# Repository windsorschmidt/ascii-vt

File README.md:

# About

Clone of Geoff Graham's ASCII video terminal. KiCad 5.2.

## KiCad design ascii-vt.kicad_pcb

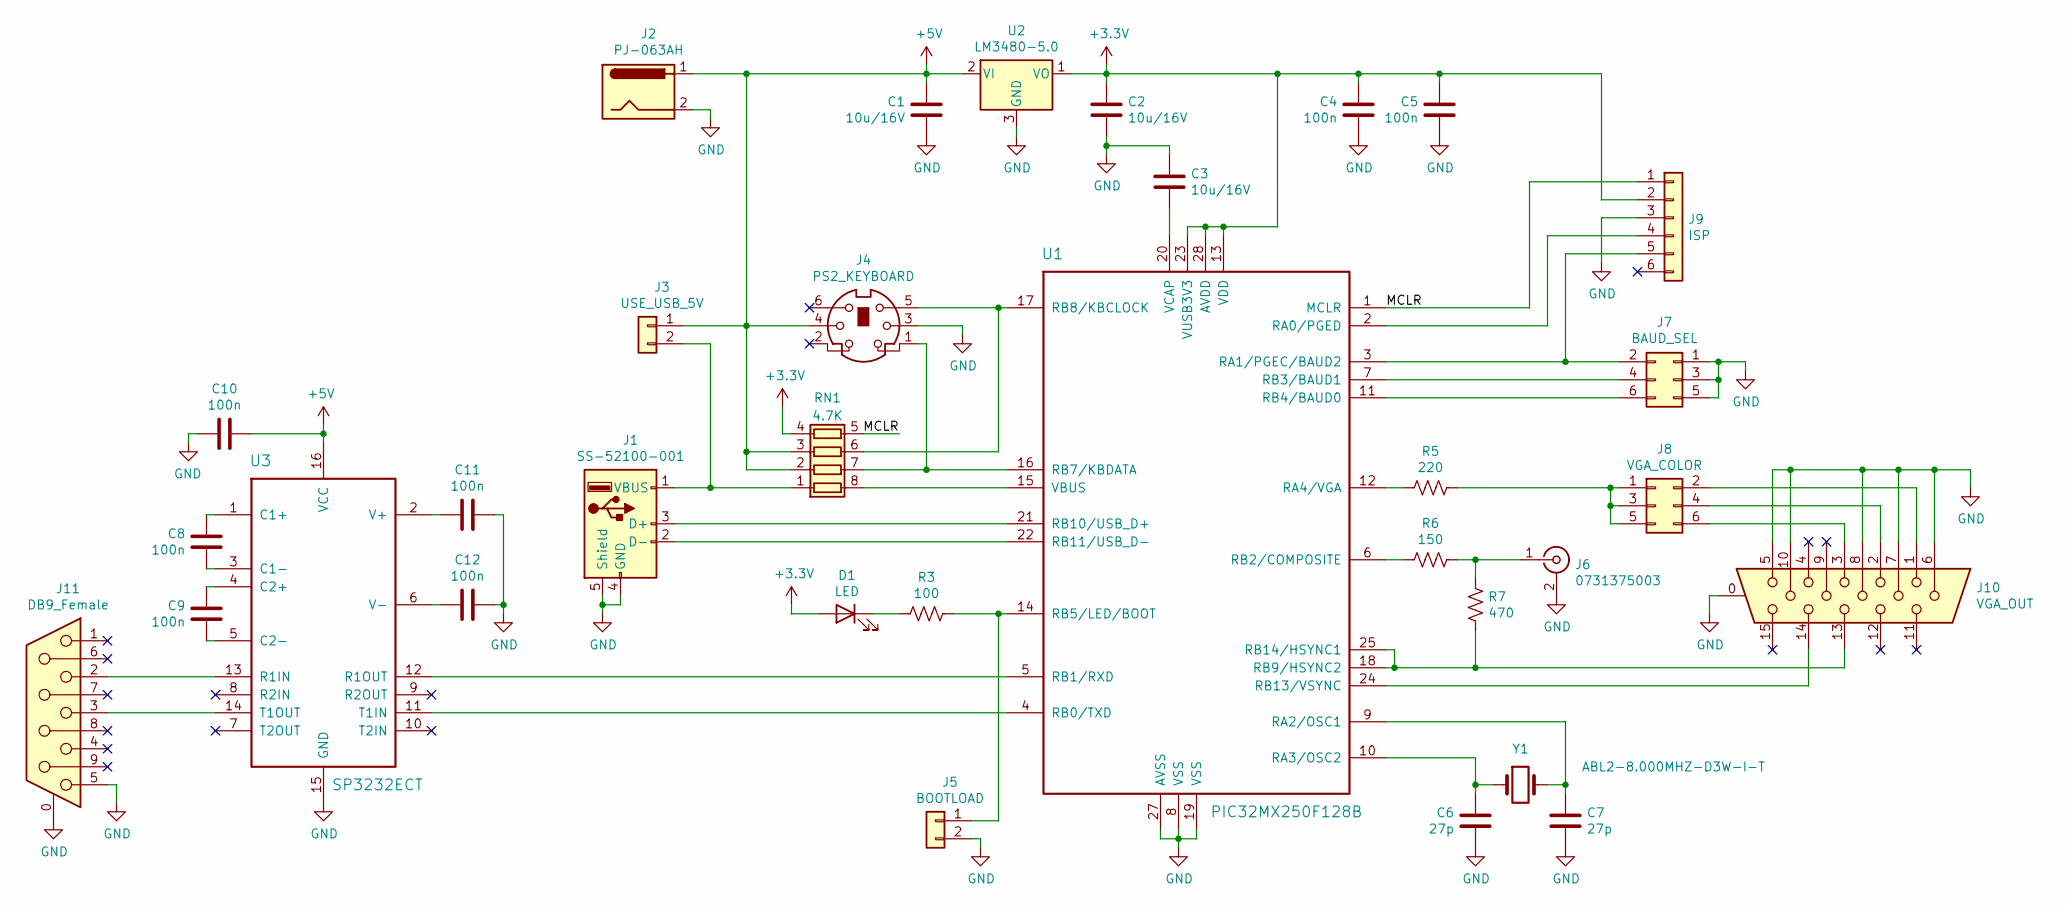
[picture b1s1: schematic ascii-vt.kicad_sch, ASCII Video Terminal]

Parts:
C1, C2, C3: 10u/16V; C_0805_2012Metric
C4, C5, C8, C9, C10, C11, C12: 100n; C_0805_2012Metric
C6, C7: 27p; C_0805_2012Metric
D1: LED; LED_0805_2012Metric
J1: SS-52100-001; USB_A_Stewart_SS-52100-001_Horizontal
J2: PJ-063AH; BarrelJack_CUI_PJ-063AH_Horizontal
J3: USE_USB_5V; PinHeader_1x02_P2.54mm_Vertical
J4: PS2_KEYBOARD; Connector_Mini-DIN_Female_6Pin_2rows
J5: BOOTLOAD; PinHeader_1x02_P2.54mm_Vertical
J6: 0731375003; BNC_Amphenol_B6252HB-NPP3G-50_Horizontal
J7: BAUD_SEL; PinHeader_2x03_P2.54mm_Vertical
J8: VGA_COLOR; PinHeader_2x03_P2.54mm_Vertical
J9: ISP; PinHeader_1x06_P2.54mm_Horizontal
J10: VGA_OUT; DSUB-15-HD_Female_Horizontal_P2.29x1.98mm_EdgePinOffset3.03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
J11: DB9_Female; DSUB-9_Female_Horizontal_P2.77x2.84mm_EdgePinOffset4.94mm_H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
R3: 100; R_0805_2012Metric
R5: 220; R_0805_2012Metric
R6: 150; R_0805_2012Metric
R7: 470; R_0805_2012Metric
RN1: 4.7K; R_Array_Convex_4x1206
U1: PIC32MX250F128B; SOIC-28W_7.5x17.9mm_P1.27mm
U2: LM3480-5.0; SOT-23
U3: SP3232ECT; SOIC-16W_7.5x10.3mm_P1.27mm
Y1: ABL2-8.000MHZ-D3W-I-T; Crystal_HC49-U_Vertical

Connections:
+3V3: C2.1, C4.2, C5.2, D1.2 (A), J9.2, RN1.4 (R4.1), U1.13 (VDD), U1.23 (VUSB3V3), U1.28 (AVDD), U2.1 (VO)
+5V: C1.2, C10.2, J2.1, J3.1, J4.4, RN1.2 (R2.1), RN1.3 (R3.1), U2.2 (VI), U3.16 (VCC)
/MCLR: J9.1, RN1.5 (R4.2), U1.1 (MCLR)
GND: C1.1, C2.2, C3.2, C4.1, C5.1, C6.2, C7.2, C10.1, C11.1, C12.1, J1.4 (GND), J1.5 (Shield), J2.2, J4.3, J5.2, J6.2 (Ext), J7.1, J7.3, J7.5, J9.3, J10.0, J10.5, J10.6, J10.7, J10.8, J10.10, J11.0 (PAD), J11.5, U1.8 (VSS), U1.19 (VSS), U1.27 (AVSS), U2.3 (GND), U3.15 (GND)
unnamed: C3.1, U1.20 (VCAP)
unnamed: C6.1, U1.10 (RA3/OSC2), Y1.1
unnamed: C7.1, U1.9 (RA2/OSC1), Y1.2
unnamed: C8.1, U3.3 (C1-)
unnamed: C8.2, U3.1 (C1+)
unnamed: C9.1, U3.5 (C2-)
unnamed: C9.2, U3.4 (C2+)
unnamed: C11.2, U3.2 (V+)
unnamed: C12.2, U3.6 (V-)
unnamed: D1.1 (K), R3.2
unnamed: J1.1 (VBUS), J3.2, RN1.1 (R1.1)
unnamed: J1.2 (D-), U1.22 (RB11/USB_D-)
unnamed: J1.3 (D+), U1.21 (RB10/USB_D+)
unnamed: J4.1, RN1.7 (R2.2), U1.16 (RB7/KBDATA)
unnamed: J4.5, RN1.6 (R3.2), U1.17 (RB8/KBCLOCK)
unnamed: J5.1, R3.1, U1.14 (RB5/LED/BOOT)
unnamed: J6.1 (In), R6.1, R7.1
unnamed: J7.2, J9.5, U1.3 (RA1/PGEC/BAUD2)
unnamed: J7.4, U1.7 (RB3/BAUD1)
unnamed: J7.6, U1.11 (RB4/BAUD0)
unnamed: J8.1, J8.3, J8.5, R5.1
unnamed: J9.4, U1.2 (RA0/PGED)
unnamed: J8.2, J10.1
unnamed: J8.4, J10.2
unnamed: J8.6, J10.3
unnamed: J10.13, R7.2, U1.18 (RB9/HSYNC2), U1.25 (RB14/HSYNC1)
unnamed: J10.14, U1.24 (RB13/VSYNC)
unnamed: J11.2, U3.13 (R1IN)
unnamed: J11.3, U3.14 (T1OUT)
unnamed: R5.2, U1.12 (RA4/VGA)
unnamed: R6.2, U1.6 (RB2/COMPOSITE)
unnamed: RN1.8 (R1.2), U1.15 (VBUS)
unnamed: U1.4 (RB0/TXD), U3.11 (T1IN)
unnamed: U1.5 (RB1/RXD), U3.12 (R1OUT)

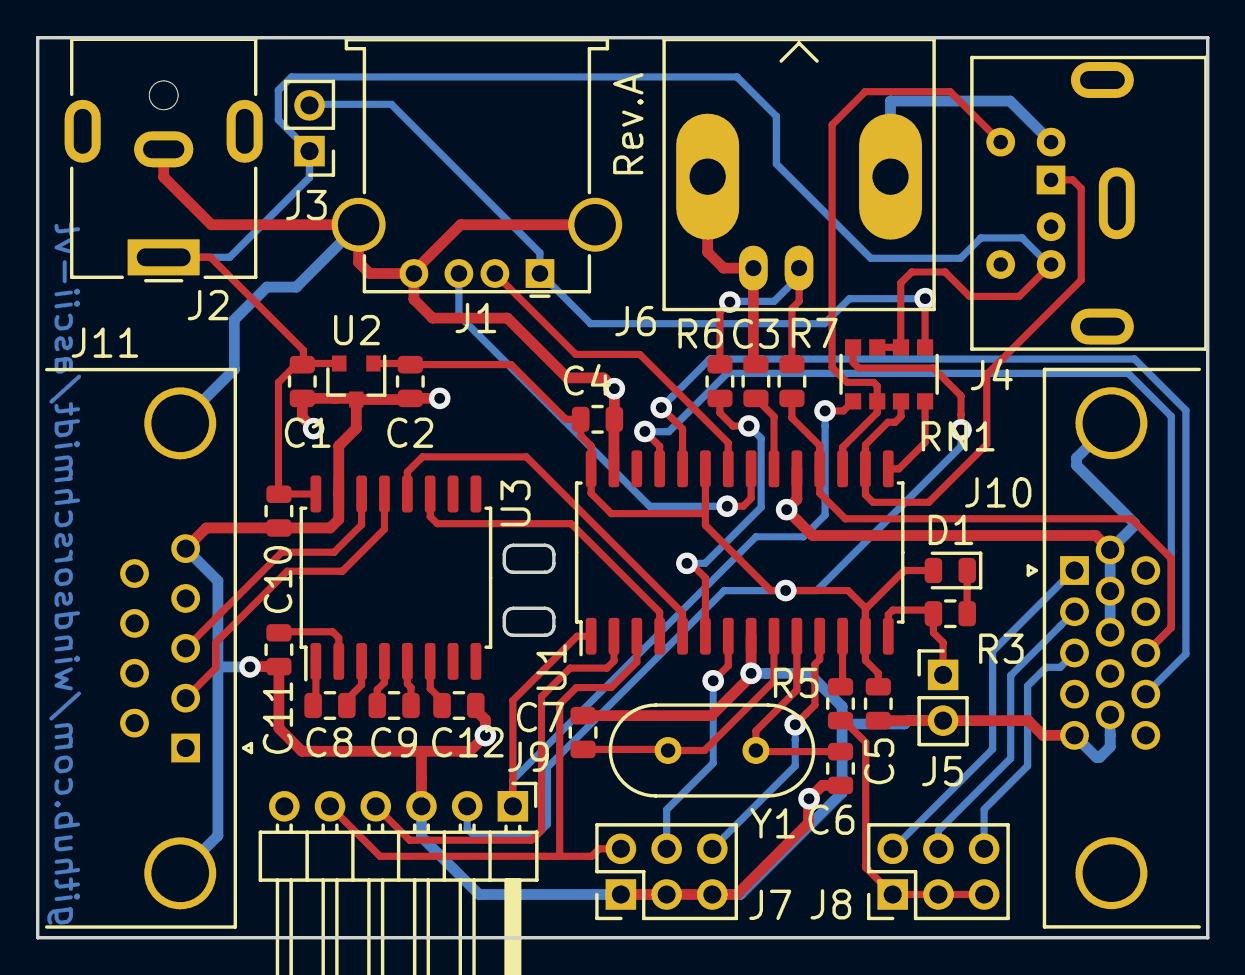
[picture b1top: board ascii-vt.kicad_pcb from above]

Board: 2 copper layers, 65.0 x 50.0 mm, 34 parts (0 on the bottom side), 38 nets.

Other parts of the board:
MNT**: Mount_Zip_Tie; MOUNT_ZIP_TIE_2X

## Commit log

2019-06-11 begin pcb layout
2019-06-11 pcb layout
2019-06-11 tweak schematic
2022-12-21 kicad 6
